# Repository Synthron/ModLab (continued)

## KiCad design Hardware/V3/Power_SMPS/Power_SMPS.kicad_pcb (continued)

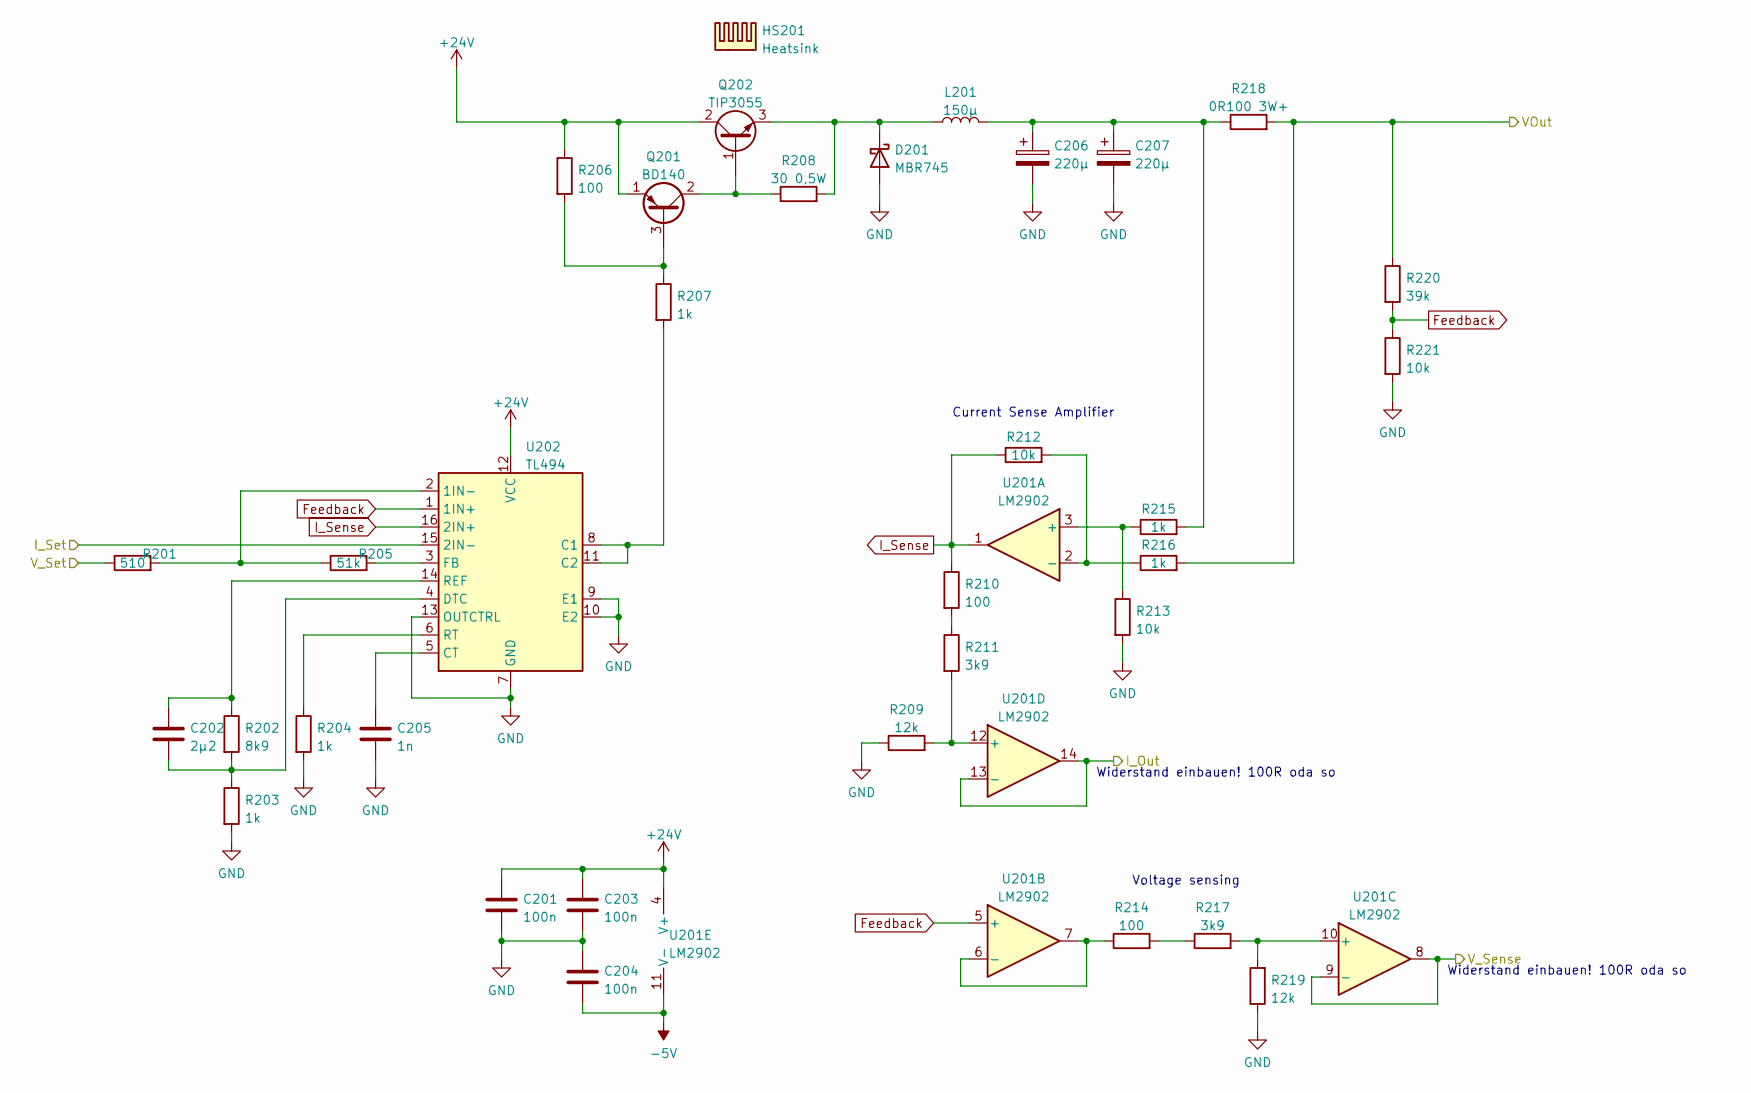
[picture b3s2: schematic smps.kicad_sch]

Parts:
C201, C203, C204: 100n; C_0805_2012Metric
C202: 2µ2; C_0805_2012Metric
C205: 1n; C_0805_2012Metric
C206, C207: 220µ; CP_Radial_D8.0mm_P5.00mm
D201: MBR745; TO-220-2_Vertical
HS201: Heatsink; SK574-50
L201: 150µ; L_Toroid_Vertical_L17.8mm_W8.1mm_P7.62mm_Bourns_5700
Q201: BD140; TO-126-3_Vertical
Q202: TIP3055; TO-218-3_Vertical
R201: 510; R_0805_2012Metric
R202: 8k9; R_0805_2012Metric
R203, R204, R207, R215, R216: 1k; R_0805_2012Metric
R205: 51k; R_0805_2012Metric
R206, R210, R214: 100; R_0805_2012Metric
R208: 30 0,5W; R_Axial_DIN0207_L6.3mm_D2.5mm_P10.16mm_Horizontal
R209, R219: 12k; R_0805_2012Metric
R211, R217: 3k9; R_0805_2012Metric
R212, R213, R221: 10k; R_0805_2012Metric
R218: 0R100 3W+; R_Axial_Power_L20.0mm_W6.4mm_P5.08mm_Vertical
R220: 39k; R_0805_2012Metric
U201: LM2902; TSSOP-14_4.4x5mm_P0.65mm
U202: TL494; SOIC-16_4.55x10.3mm_P1.27mm

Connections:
+24V: C201.1, C203.1, Q201.1 (E), Q202.2 (C), R206.1, U201.4 (V+), U202.12 (VCC); also elsewhere on the board
-5V: C204.2, U201.11 (V-); also elsewhere on the board
/CPU/I+: U201.13 (-), U201.14; also elsewhere on the board
/CPU/ISET: U202.15 (2IN-); also elsewhere on the board
/CPU/V+: U201.8, U201.9 (-); also elsewhere on the board
/CPU/VSET: R201.1; also elsewhere on the board
/SMPS/VOut: R216.2, R218.2, R220.1; also elsewhere on the board
Feedback: R220.2, R221.1, U201.5 (+), U202.1 (1IN+)
GND: C201.2, C203.2, C204.1, C205.2, C206.2, C207.2, D201.2 (A), R203.2, R204.2, R209.1, R213.2, R219.1, R221.2, U202.7 (GND), U202.9 (E1), U202.10 (E2), U202.13 (OUTCTRL); also elsewhere on the board
I_Sense: R210.1, R212.1, U201.1, U202.16 (2IN+)
unnamed: C202.1, R202.1, U202.14 (REF)
unnamed: C202.2, R202.2, R203.1, U202.4 (DTC)
unnamed: C205.1, U202.5 (CT)
unnamed: C206.1, C207.1, L201.2, R215.2, R218.1
unnamed: D201.1 (K), L201.1, Q202.3 (E), R208.2
unnamed: Q201.2 (C), Q202.1 (B), R208.1
unnamed: Q201.3 (B), R206.2, R207.1
unnamed: R201.2, R205.1, U202.2 (1IN-)
unnamed: R204.1, U202.6 (RT)
unnamed: R205.2, U202.3 (FB)
unnamed: R207.2, U202.8 (C1), U202.11 (C2)
unnamed: R209.2, R211.2, U201.12 (+)
unnamed: R210.2, R211.1
unnamed: R212.2, R216.1, U201.2 (-)
unnamed: R213.1, R215.1, U201.3 (+)
unnamed: R214.1, U201.6 (-), U201.7
unnamed: R214.2, R217.1
unnamed: R217.2, R219.2, U201.10 (+)

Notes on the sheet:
Widerstand einbauen! 100R oda so
Current Sense Amplifier
Voltage sensing

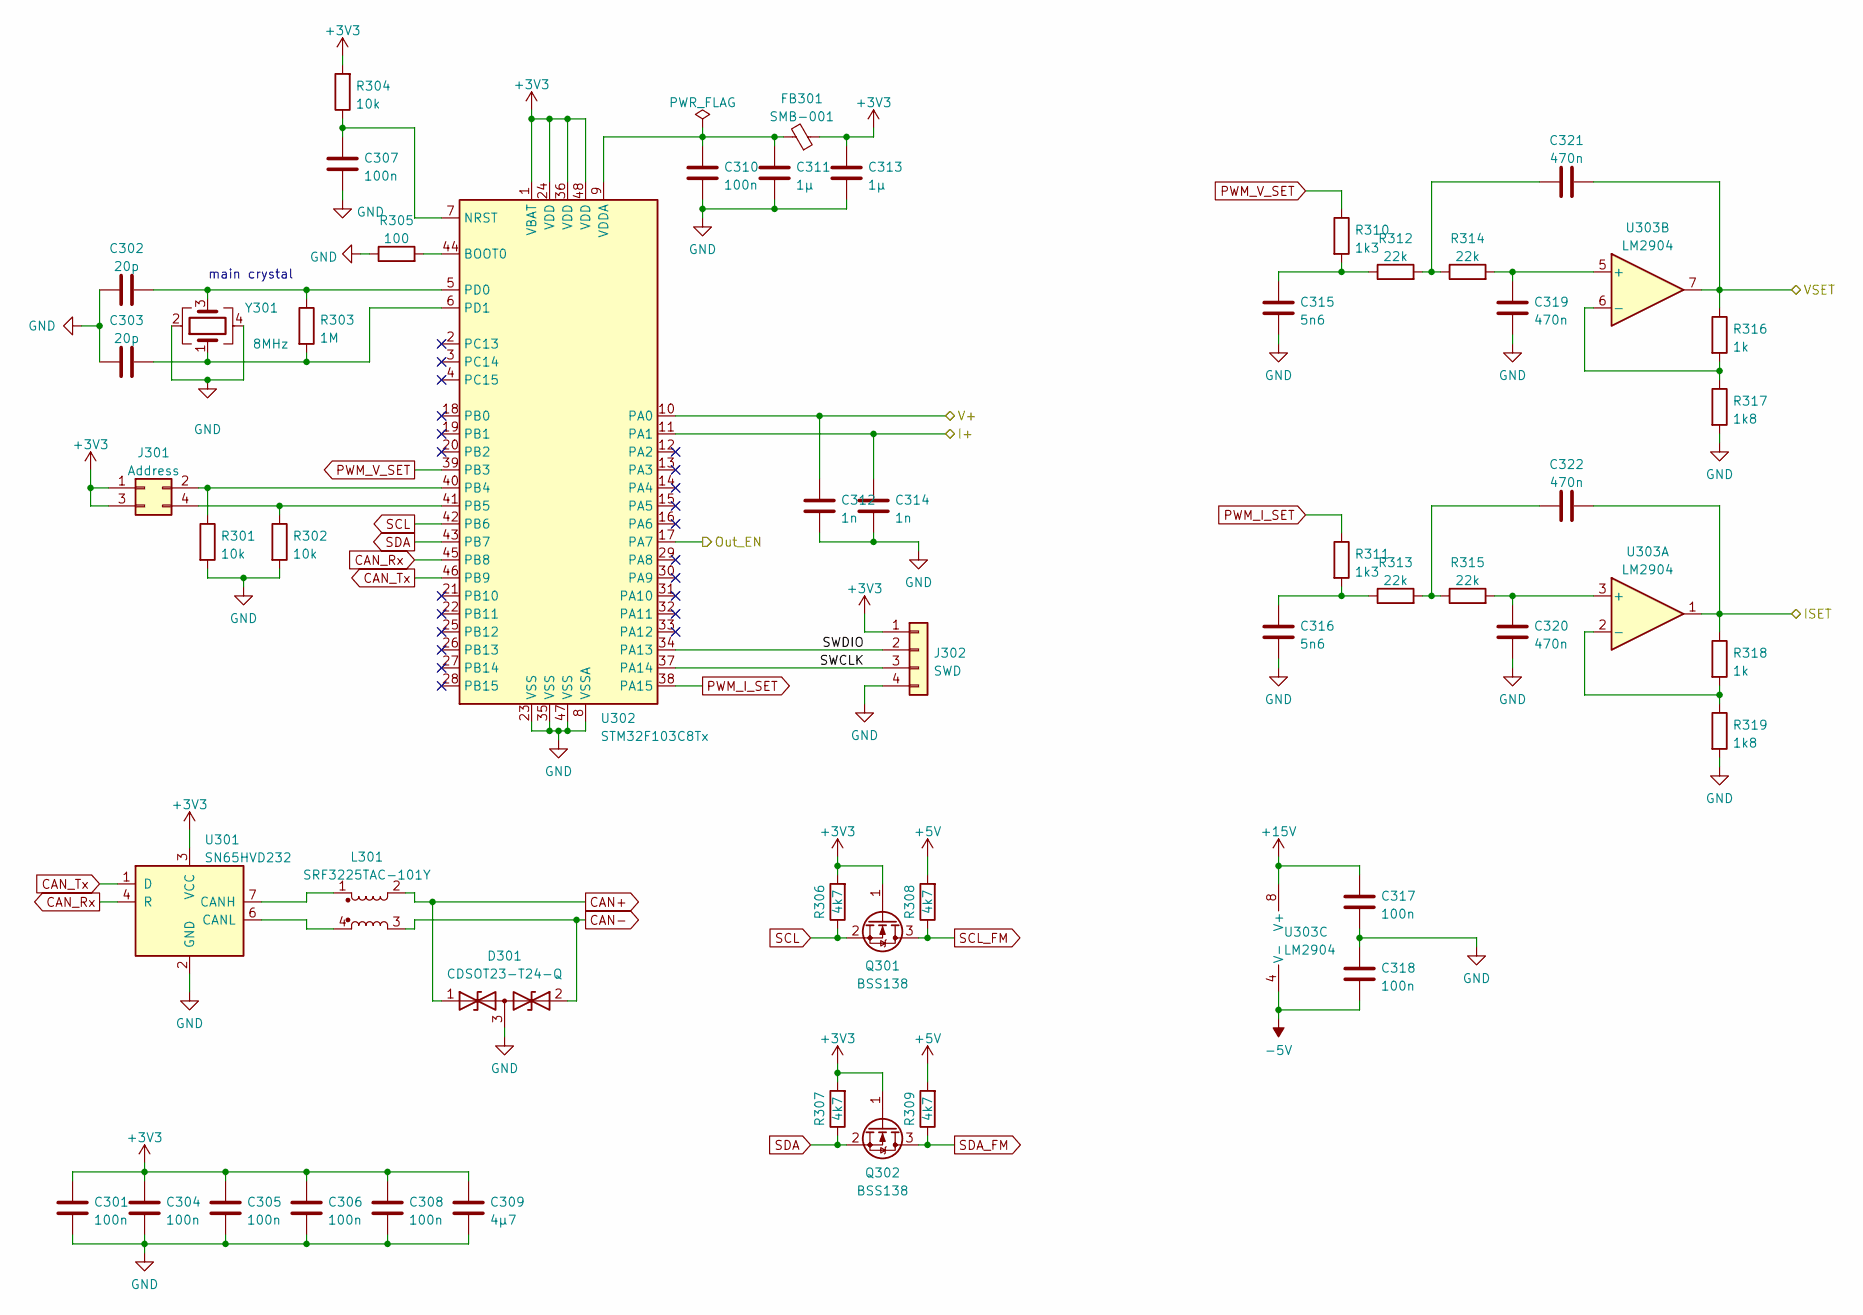
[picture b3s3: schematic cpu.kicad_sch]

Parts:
C301, C304, C305, C306, C307, C308, C310, C317, C318: 100n; C_0805_2012Metric
C302, C303: 20p; C_0805_2012Metric
C309: 4µ7; C_0805_2012Metric
C311, C313: 1µ; C_0805_2012Metric
C312, C314: 1n; C_0805_2012Metric
C315, C316: 5n6; C_0805_2012Metric
C319, C320, C321, C322: 470n; C_0805_2012Metric
D301: CDSOT23-T24-Q; SOT-23
FB301: SMB-001
J301: Address; PinHeader_2x02_P2.54mm_Vertical
J302: SWD; JST_XH_B4B-XH-A_1x04_P2.50mm_Vertical
L301: SRF3225TAC-101Y; SRF3225TAC
Q301, Q302: BSS138; SOT-23
R301, R302, R304: 10k; R_0805_2012Metric
R303: 1M; R_0805_2012Metric
R305: 100; R_0805_2012Metric
R306, R307, R308, R309: 4k7; R_0805_2012Metric
R310, R311: 1k3; R_0805_2012Metric
R312, R313, R314, R315: 22k; R_0805_2012Metric
R316, R318: 1k; R_0805_2012Metric
R317, R319: 1k8; R_0805_2012Metric
U301: SN65HVD232; SOIC-8_3.9x4.9mm_P1.27mm
U302: STM32F103C8Tx; LQFP-48_7x7mm_P0.5mm
U303: LM2904; SOIC-8_5.23x5.23mm_P1.27mm
Y301: 8MHz; Crystal_SMD_5032-4Pin_5.0x3.2mm

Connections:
+3V3: C301.1, C304.1, C305.1, C306.1, C308.1, C309.1, C313.1, FB301.1, J301.1, J301.3, J302.1, Q301.1 (G), Q302.1 (G), R304.2, R306.2, R307.2, U301.3 (VCC), U302.1 (VBAT), U302.24 (VDD), U302.36 (VDD), U302.48 (VDD); also elsewhere on the board
+5V: R308.2, R309.2; also elsewhere on the board
+15V: C317.1, U303.8 (V+); also elsewhere on the board
-5V: C318.2, U303.4 (V-); also elsewhere on the board
/CPU/I+: C314.1, U302.11 (PA1); also elsewhere on the board
/CPU/ISET: C322.2, R318.1, U303.1; also elsewhere on the board
/CPU/Out_EN: U302.17 (PA7); also elsewhere on the board
/CPU/SWCLK: J302.3, U302.37 (PA14)
/CPU/SWDIO: J302.2, U302.34 (PA13)
/CPU/V+: C312.1, U302.10 (PA0); also elsewhere on the board
/CPU/VSET: C321.2, R316.1, U303.7; also elsewhere on the board
CAN+: D301.1 (A1), L301.2; also elsewhere on the board
CAN-: D301.2 (A2), L301.3; also elsewhere on the board
CAN_Rx: U301.4 (R), U302.45 (PB8)
CAN_Tx: U301.1 (D), U302.46 (PB9)
GND: C301.2, C302.1, C303.1, C304.2, C305.2, C306.2, C307.2, C308.2, C309.2, C310.2, C311.2, C312.2, C313.2, C314.2, C315.2, C316.2, C317.2, C318.1, C319.2, C320.2, D301.3 (common), J302.4, R301.2, R302.2, R305.1, R317.2, R319.2, U301.2 (GND), U302.8 (VSSA), U302.23 (VSS), U302.35 (VSS), U302.47 (VSS), Y301.2, Y301.4; also elsewhere on the board
unnamed: C302.2, R303.1, U302.5 (PD0), Y301.3
unnamed: C303.2, R303.2, U302.6 (PD1), Y301.1
unnamed: C307.1, R304.1, U302.7 (NRST)
unnamed: C310.1, C311.1, FB301.2, U302.9 (VDDA)
unnamed: C315.1, R310.2, R312.1
unnamed: C316.1, R311.2, R313.1
unnamed: C319.1, R314.2, U303.5 (+)
unnamed: C320.1, R315.2, U303.3 (+)
unnamed: C321.1, R312.2, R314.1
unnamed: C322.1, R313.2, R315.1
unnamed: J301.2, R301.1, U302.40 (PB4)
unnamed: J301.4, R302.1, U302.41 (PB5)
unnamed: L301.1, U301.7 (CANH)
unnamed: L301.4, U301.6 (CANL)
unnamed: R305.2, U302.44 (BOOT0)
unnamed: R316.2, R317.1, U303.6 (-)
unnamed: R318.2, R319.1, U303.2 (-)
PWM_I_SET: R311.1, U302.38 (PA15)
PWM_V_SET: R310.1, U302.39 (PB3)
SCL: Q301.2 (S), R306.1, U302.42 (PB6)
SCL_FM: Q301.3 (D), R308.1; also elsewhere on the board
SDA: Q302.2 (S), R307.1, U302.43 (PB7)
SDA_FM: Q302.3 (D), R309.1; also elsewhere on the board

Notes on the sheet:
main crystal

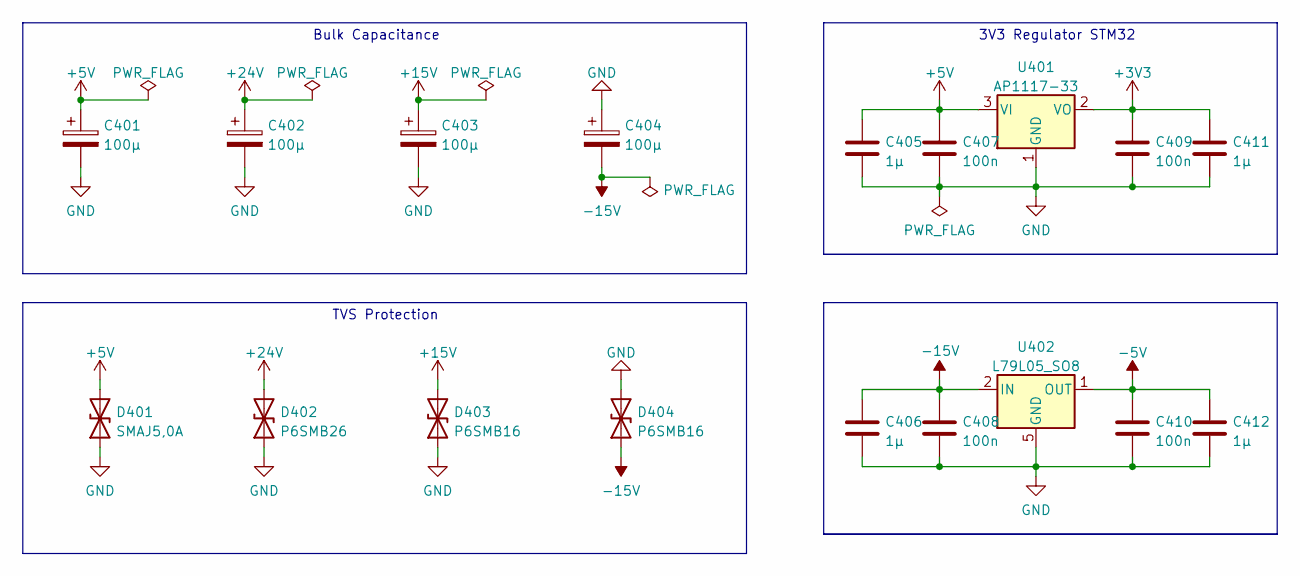
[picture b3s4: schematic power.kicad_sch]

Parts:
C401, C402, C403, C404: 100µ; CP_Radial_D8.0mm_P5.00mm
C405, C406, C411, C412: 1µ; C_0805_2012Metric
C407, C408, C409, C410: 100n; C_0805_2012Metric
D401: SMAJ5,0A; D_SMA
D402: P6SMB26; D_SMA
D403, D404: P6SMB16; D_SMA
U401: AP1117-33; SOT-223-3_TabPin2
U402: L79L05_SO8; SOIC-8_3.9x4.9mm_P1.27mm

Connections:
+3V3: C409.1, C411.1, U401.2 (VO); also elsewhere on the board
+5V: C401.1, C405.1, C407.1, D401.2 (A2), U401.3 (VI); also elsewhere on the board
+15V: C403.1, D403.2 (A2); also elsewhere on the board
+24V: C402.1, D402.2 (A2); also elsewhere on the board
-5V: C410.1, C412.1, U402.1 (OUT); also elsewhere on the board
-15V: C404.2, C406.1, C408.1, D404.1 (A1), U402.2 (IN), U402.3 (IN), U402.6 (IN), U402.7 (IN); also elsewhere on the board
GND: C401.2, C402.2, C403.2, C404.1, C405.2, C406.2, C407.2, C408.2, C409.2, C410.2, C411.2, C412.2, D401.1 (A1), D402.1 (A1), D403.1 (A1), D404.2 (A2), U401.1 (GND), U402.5 (GND); also elsewhere on the board

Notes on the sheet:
3V3 Regulator STM32
Bulk Capacitance
TVS Protection

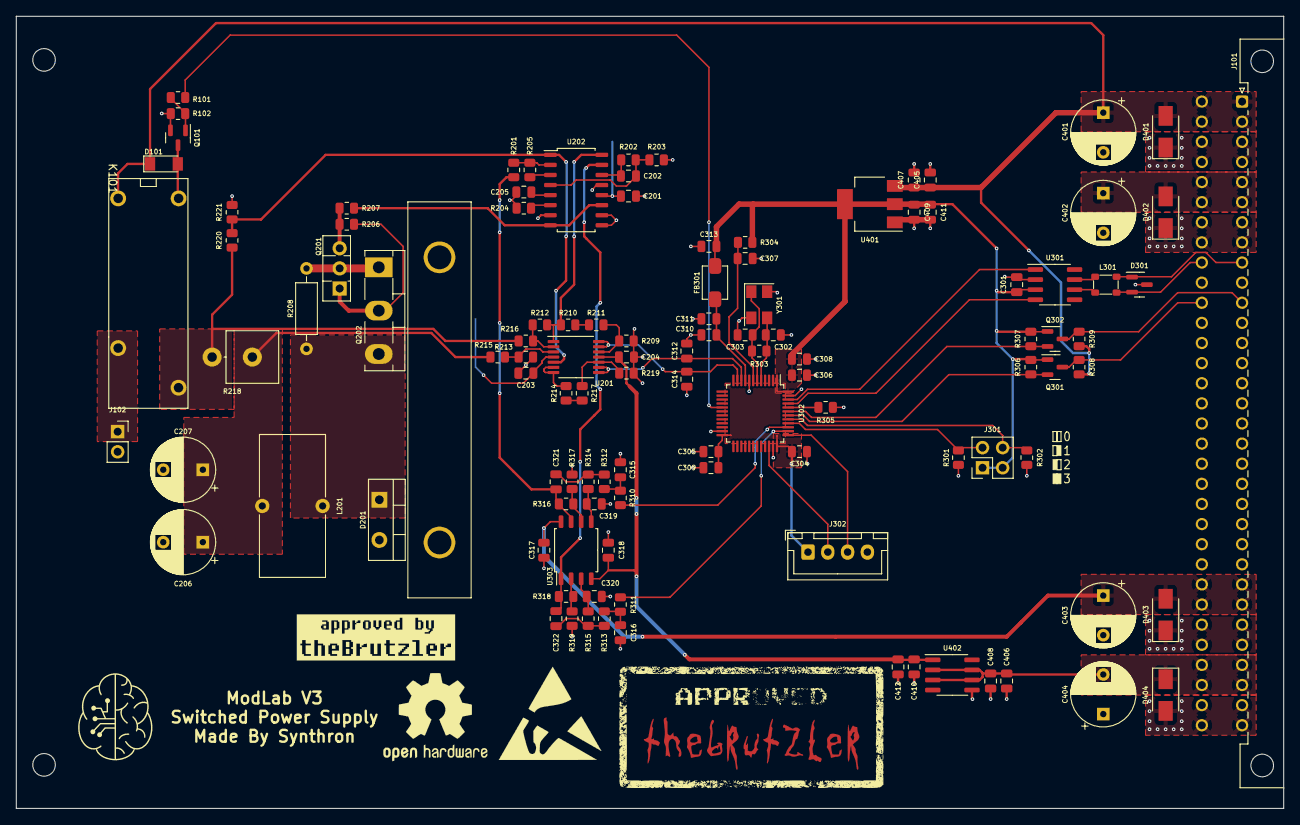
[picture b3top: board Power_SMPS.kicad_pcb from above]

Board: 2 copper layers, 160.0 x 100.0 mm, 112 parts (0 on the bottom side), 65 nets.

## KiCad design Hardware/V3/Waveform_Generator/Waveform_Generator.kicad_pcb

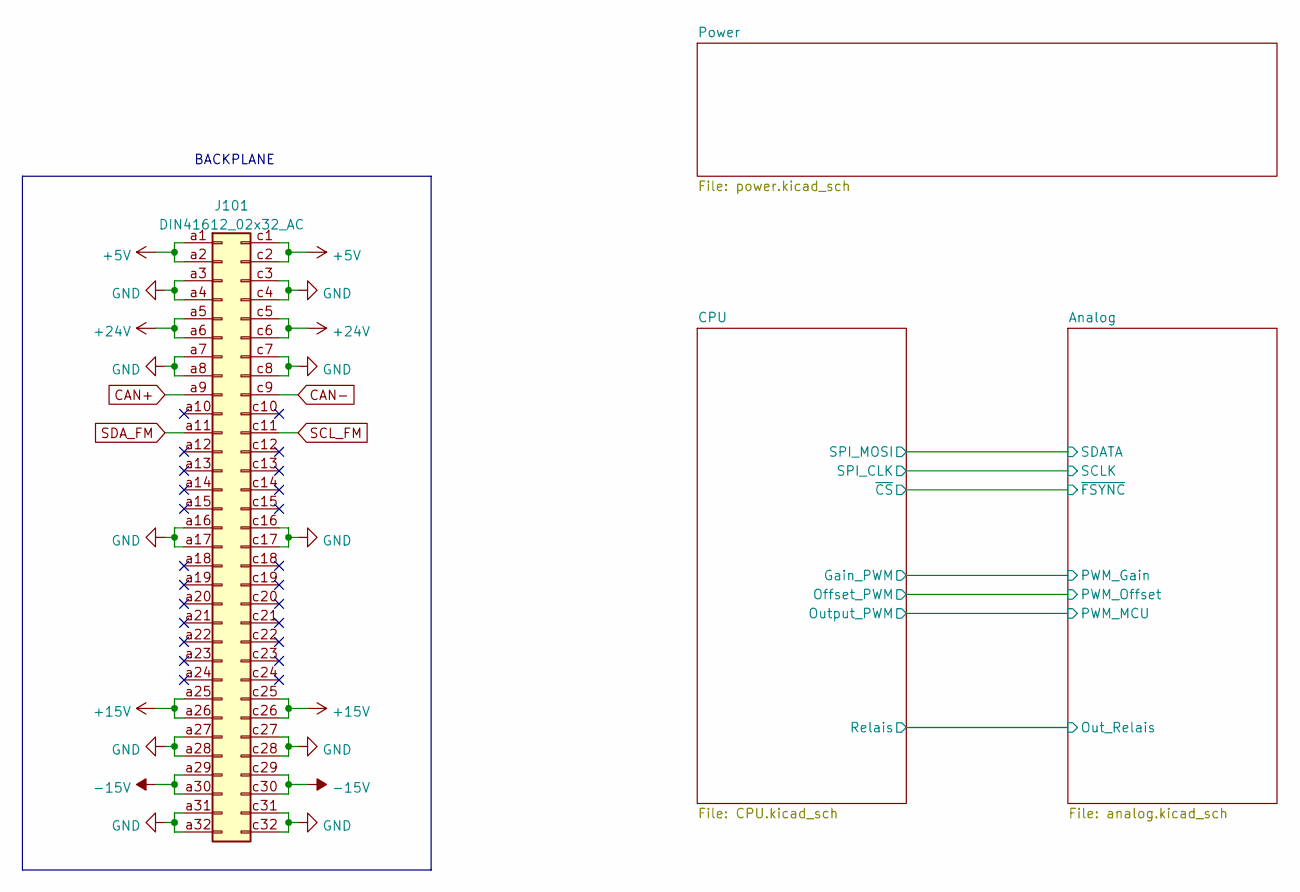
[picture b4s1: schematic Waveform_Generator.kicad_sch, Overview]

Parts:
J101: DIN41612_02x32_AC; VG64_Euro

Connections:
+5V: J101.a1, J101.a2, J101.c1, J101.c2; also elsewhere on the board
+15V: J101.a25, J101.a26, J101.c25, J101.c26; also elsewhere on the board
+24V: J101.a5, J101.a6, J101.c5, J101.c6; also elsewhere on the board
-15V: J101.a29, J101.a30, J101.c29, J101.c30; also elsewhere on the board
CAN+: J101.a9; also elsewhere on the board
CAN-: J101.c9; also elsewhere on the board
GND: J101.a3, J101.a4, J101.a7, J101.a8, J101.a16, J101.a17, J101.a27, J101.a28, J101.a31, J101.a32, J101.c3, J101.c4, J101.c7, J101.c8, J101.c16, J101.c17, J101.c27, J101.c28, J101.c31, J101.c32; also elsewhere on the board
SCL_FM: J101.c11; also elsewhere on the board
SDA_FM: J101.a11; also elsewhere on the board

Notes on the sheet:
BACKPLANE

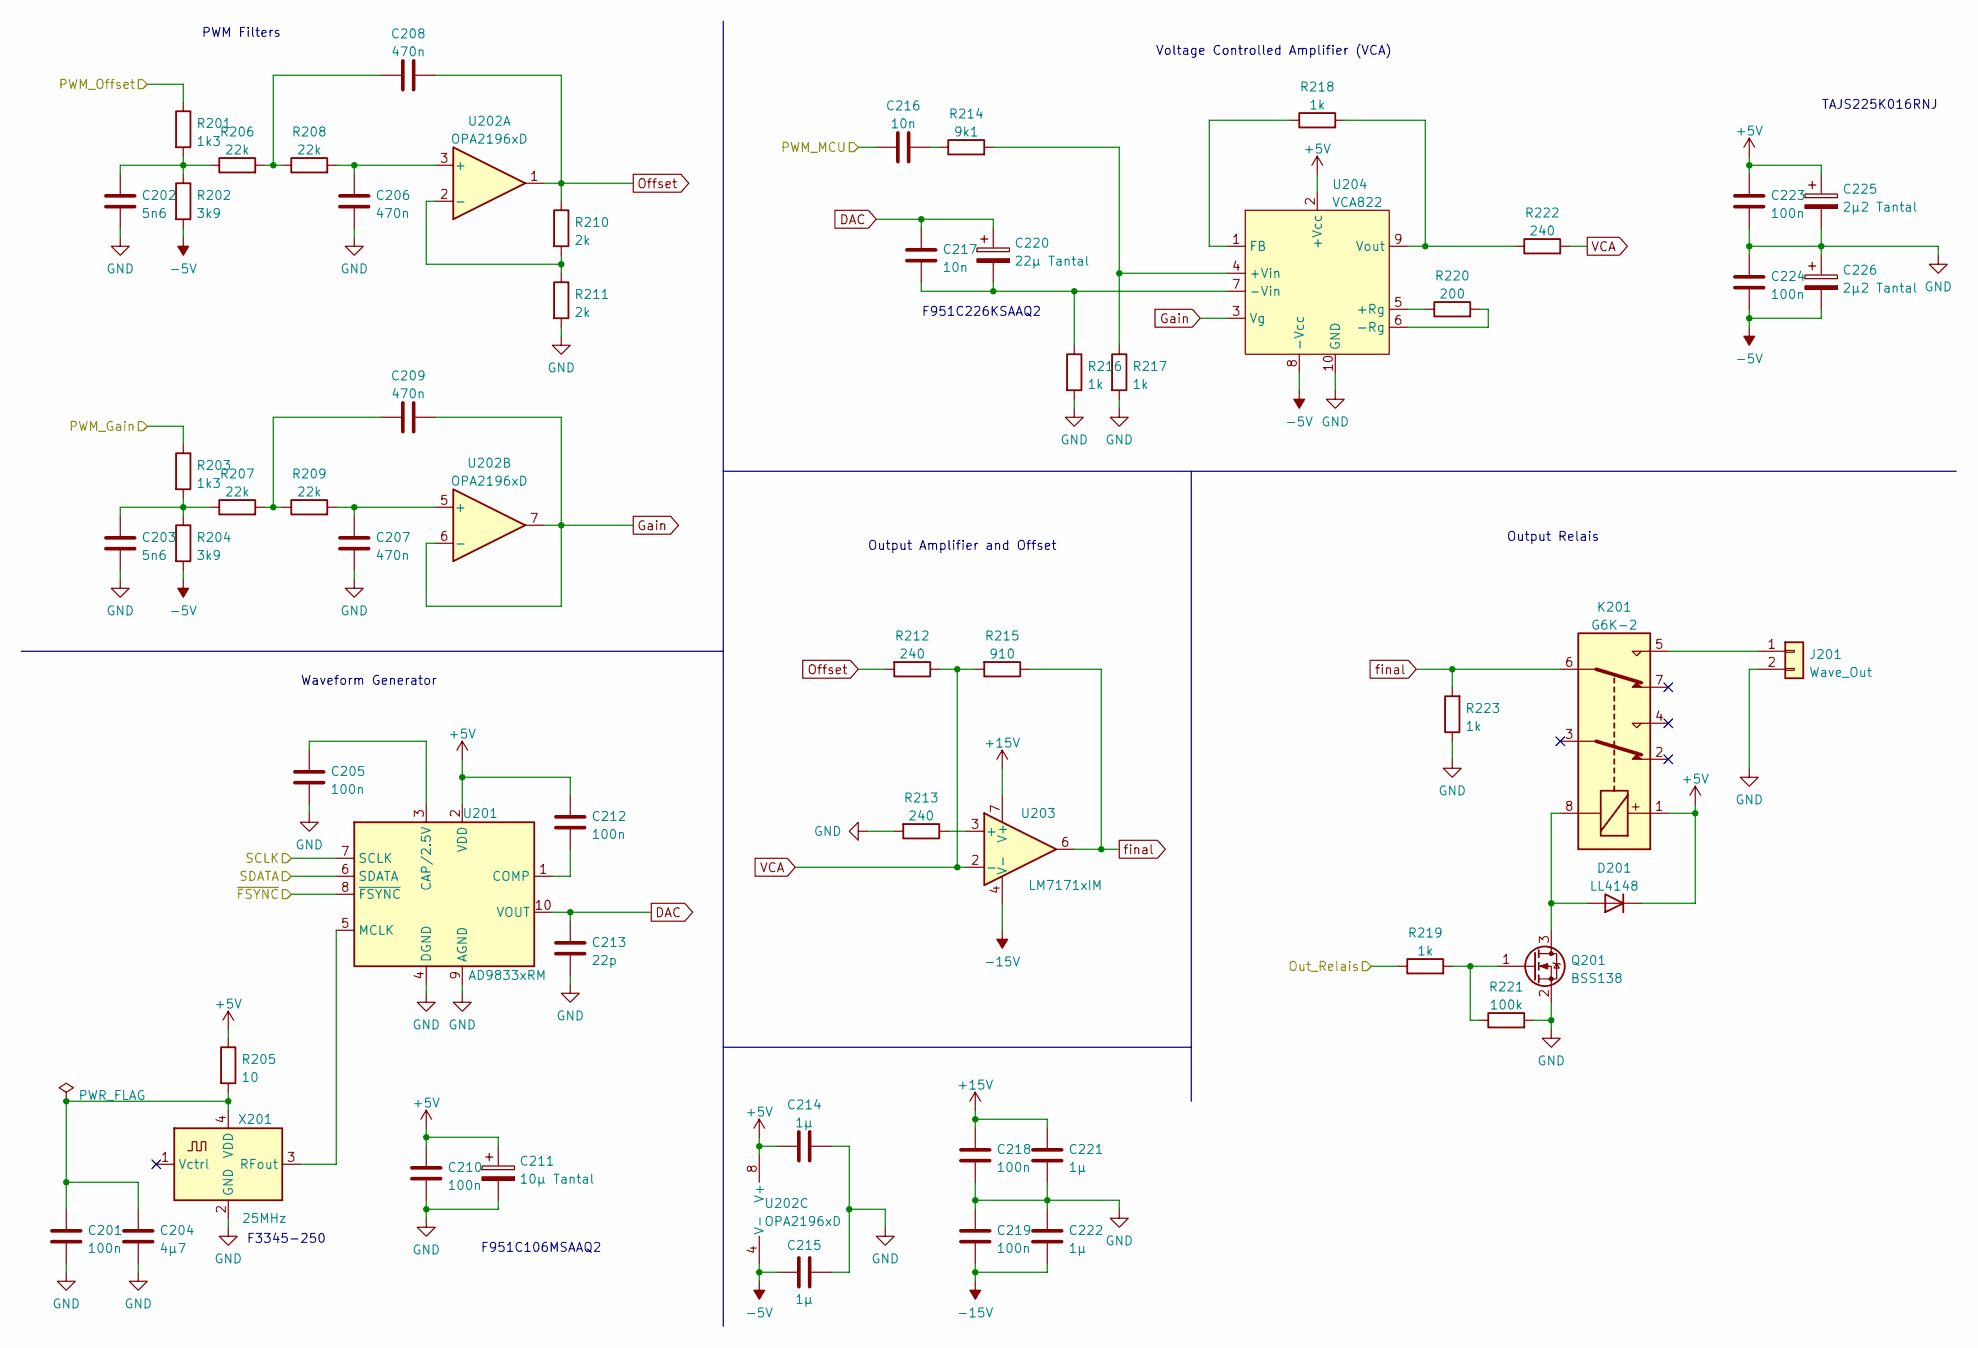
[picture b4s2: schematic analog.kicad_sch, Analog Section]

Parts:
C201, C205, C210, C212, C218, C219, C223, C224: 100n; C_0805_2012Metric
C202, C203: 5n6; C_0805_2012Metric
C204: 4µ7; C_0805_2012Metric
C206, C207, C208, C209: 470n; C_0805_2012Metric
C211: 10µ Tantal; CP_EIA-3216-12_Kemet-S
C213: 22p; C_0805_2012Metric
C214, C215, C221, C222: 1µ; C_0805_2012Metric
C216, C217: 10n; C_0805_2012Metric
C220: 22µ Tantal; CP_EIA-3216-12_Kemet-S
C225, C226: 2µ2 Tantal; CP_EIA-3216-12_Kemet-S
D201: LL4148; D_MiniMELF
J201: Wave_Out; PinSocket_1x02_P2.54mm_Vertical
K201: G6K-2; Relay_DPDT_Omron_G6K-2F
Q201: BSS138; SOT-23
R201, R203: 1k3; R_0805_2012Metric
R202, R204: 3k9; R_0805_2012Metric
R205: 10; R_0805_2012Metric
R206, R207, R208, R209: 22k; R_0805_2012Metric
R210, R211: 2k; R_0805_2012Metric
R212, R213, R222: 240; R_0805_2012Metric
R214: 9k1; R_0805_2012Metric
R215: 910; R_0805_2012Metric
R216, R217, R218, R219, R223: 1k; R_0805_2012Metric
R220: 200; R_0805_2012Metric
R221: 100k; R_0805_2012Metric
U201: AD9833xRM; MSOP-10_3x3mm_P0.5mm
U202: OPA2196xD; SOIC-8_3.9x4.9mm_P1.27mm
U203: LM7171xIM; SOIC-8_3.9x4.9mm_P1.27mm
U204: VCA822; MSOP-10_3x3mm_P0.5mm
X201: 25MHz; Oscillator_SMD_EuroQuartz_XO91-4Pin_7.0x5.0mm

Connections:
+5V: C210.1, C211.1, C212.1, C214.1, C223.1, C225.1, D201.1 (K), K201.1, R205.1, U201.2 (VDD), U202.8 (V+), U204.2 (+Vcc); also elsewhere on the board
+15V: C218.1, C221.1, U203.7 (V+); also elsewhere on the board
-5V: C215.1, C224.2, C226.2, R202.2, R204.2, U202.4 (V-), U204.8 (-Vcc); also elsewhere on the board
-15V: C219.2, C222.2, U203.4 (V-); also elsewhere on the board
/Analog/Out_Relais: R219.1; also elsewhere on the board
/Analog/PWM_Gain: R203.1; also elsewhere on the board
/Analog/PWM_MCU: C216.1; also elsewhere on the board
/Analog/PWM_Offset: R201.1; also elsewhere on the board
/Analog/SCLK: U201.7 (SCLK); also elsewhere on the board
/Analog/SDATA: U201.6 (SDATA); also elsewhere on the board
/Analog/~FSYNC: U201.8 (~FSYNC); also elsewhere on the board
DAC: C213.1, C217.1, C220.1, U201.10 (VOUT)
GND: C201.2, C202.2, C203.2, C204.2, C205.2, C206.2, C207.2, C210.2, C211.2, C213.2, C214.2, C215.2, C218.2, C219.1, C221.2, C222.1, C223.2, C224.1, C225.2, C226.1, J201.2, Q201.2 (S), R211.2, R213.2, R216.2, R217.2, R221.2, R223.1, U201.4 (DGND), U201.9 (AGND), U204.10 (GND), X201.2 (GND); also elsewhere on the board
Gain: C209.2, U202.6 (-), U202.7, U204.3 (Vg)
unnamed: C201.1, C204.1, R205.2, X201.4 (VDD)
unnamed: C202.1, R201.2, R202.1, R206.1
unnamed: C203.1, R203.2, R204.1, R207.1
unnamed: C205.1, U201.3 (CAP/2.5V)
unnamed: C206.1, R208.2, U202.3 (+)
unnamed: C207.1, R209.2, U202.5 (+)
unnamed: C208.1, R206.2, R208.1
unnamed: C209.1, R207.2, R209.1
unnamed: C212.2, U201.1 (COMP)
unnamed: C216.2, R214.1
unnamed: C217.2, C220.2, R216.1, U204.7 (-Vin)
unnamed: D201.2 (A), K201.8, Q201.3 (D)
unnamed: J201.1, K201.5
unnamed: Q201.1 (G), R219.2, R221.1
unnamed: R210.2, R211.1, U202.2 (-)
unnamed: R213.1, U203.3 (+)
unnamed: R214.2, R217.1, U204.4 (+Vin)
unnamed: R218.1, U204.1 (FB)
unnamed: R218.2, R222.1, U204.9 (Vout)
unnamed: R220.1, U204.5 (+Rg)
unnamed: R220.2, U204.6 (-Rg)
unnamed: U201.5 (MCLK), X201.3 (RFout)
Offset: C208.2, R210.1, R212.2, U202.1
VCA: R212.1, R215.2, R222.2, U203.2 (-)
final: K201.6, R215.1, R223.2, U203.6

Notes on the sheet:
PWM Filters
TAJS225K016RNJ
Output Amplifier and Offset
Waveform Generator
Voltage Controlled Amplifier (VCA)
F951C226KSAAQ2
Output Relais
F3345-250
F951C106MSAAQ2

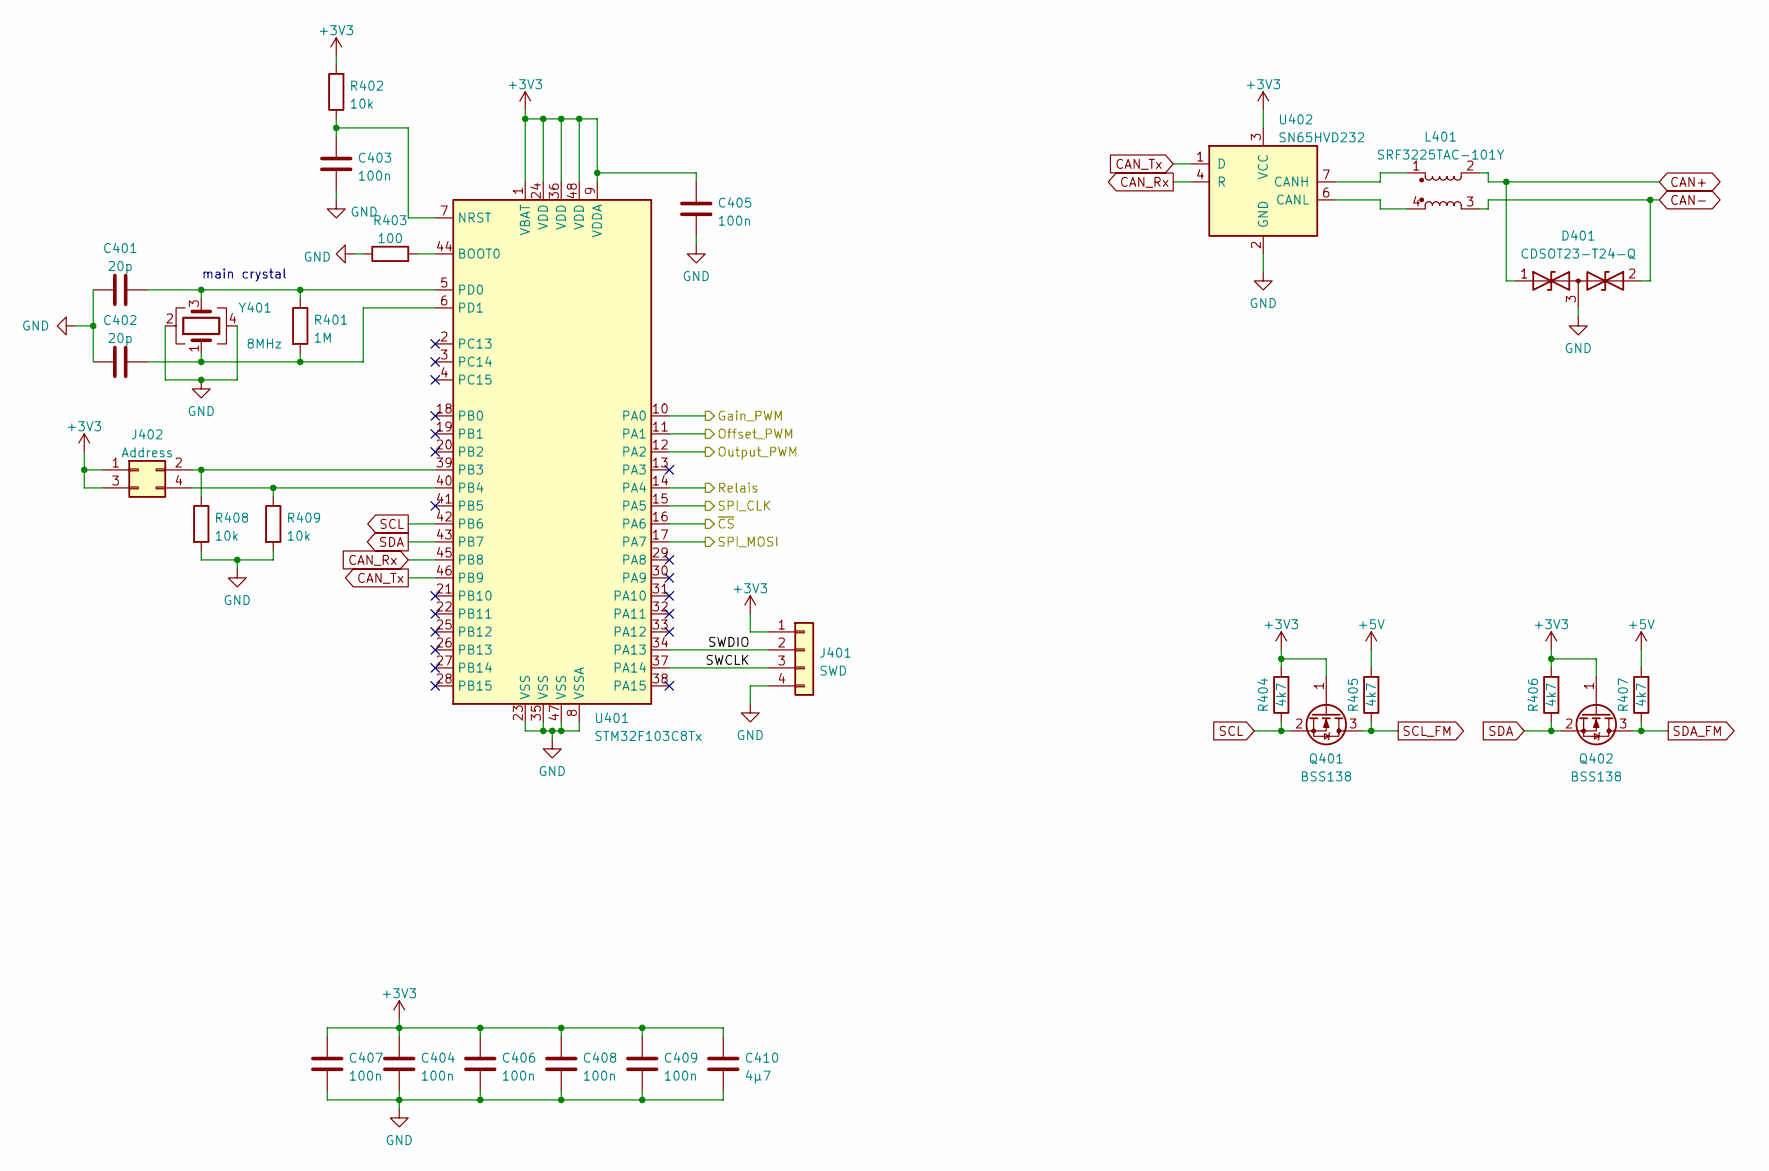
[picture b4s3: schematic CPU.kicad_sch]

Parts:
C401, C402: 20p; C_0805_2012Metric
C403, C404, C405, C406, C407, C408, C409: 100n; C_0805_2012Metric
C410: 4µ7; C_0805_2012Metric
D401: CDSOT23-T24-Q; SOT-23
J401: SWD; JST_XH_B4B-XH-A_1x04_P2.50mm_Vertical
J402: Address; PinHeader_2x02_P2.54mm_Vertical
L401: SRF3225TAC-101Y; SRF3225TAC
Q401, Q402: BSS138; SOT-23
R401: 1M; R_0805_2012Metric
R402, R408, R409: 10k; R_0805_2012Metric
R403: 100; R_0805_2012Metric
R404, R405, R406, R407: 4k7; R_0805_2012Metric
U401: STM32F103C8Tx; LQFP-48_7x7mm_P0.5mm
U402: SN65HVD232; SOIC-8_3.9x4.9mm_P1.27mm
Y401: 8MHz; Crystal_SMD_5032-4Pin_5.0x3.2mm

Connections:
+3V3: C404.1, C405.1, C406.1, C407.1, C408.1, C409.1, C410.1, J401.1, J402.1, J402.3, Q401.1 (G), Q402.1 (G), R402.2, R404.2, R406.2, U401.1 (VBAT), U401.9 (VDDA), U401.24 (VDD), U401.36 (VDD), U401.48 (VDD), U402.3 (VCC); also elsewhere on the board
+5V: R405.2, R407.2; also elsewhere on the board
/Analog/Out_Relais: U401.14 (PA4); also elsewhere on the board
/Analog/PWM_Gain: U401.10 (PA0); also elsewhere on the board
/Analog/PWM_MCU: U401.12 (PA2); also elsewhere on the board
/Analog/PWM_Offset: U401.11 (PA1); also elsewhere on the board
/Analog/SCLK: U401.15 (PA5); also elsewhere on the board
/Analog/SDATA: U401.17 (PA7); also elsewhere on the board
/Analog/~FSYNC: U401.16 (PA6); also elsewhere on the board
/CPU/SWCLK: J401.3, U401.37 (PA14)
/CPU/SWDIO: J401.2, U401.34 (PA13)
CAN+: D401.1 (A1), L401.2; also elsewhere on the board
CAN-: D401.2 (A2), L401.3; also elsewhere on the board
CAN_Rx: U401.45 (PB8), U402.4 (R)
CAN_Tx: U401.46 (PB9), U402.1 (D)
GND: C401.1, C402.1, C403.2, C404.2, C405.2, C406.2, C407.2, C408.2, C409.2, C410.2, D401.3 (common), J401.4, R403.1, R408.2, R409.2, U401.8 (VSSA), U401.23 (VSS), U401.35 (VSS), U401.47 (VSS), U402.2 (GND), Y401.2, Y401.4; also elsewhere on the board
unnamed: C401.2, R401.1, U401.5 (PD0), Y401.3
unnamed: C402.2, R401.2, U401.6 (PD1), Y401.1
unnamed: C403.1, R402.1, U401.7 (NRST)
unnamed: J402.2, R408.1, U401.39 (PB3)
unnamed: J402.4, R409.1, U401.40 (PB4)
unnamed: L401.1, U402.7 (CANH)
unnamed: L401.4, U402.6 (CANL)
unnamed: R403.2, U401.44 (BOOT0)
SCL: Q401.2 (S), R404.1, U401.42 (PB6)
SCL_FM: Q401.3 (D), R405.1; also elsewhere on the board
SDA: Q402.2 (S), R406.1, U401.43 (PB7)
SDA_FM: Q402.3 (D), R407.1; also elsewhere on the board

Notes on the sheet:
main crystal

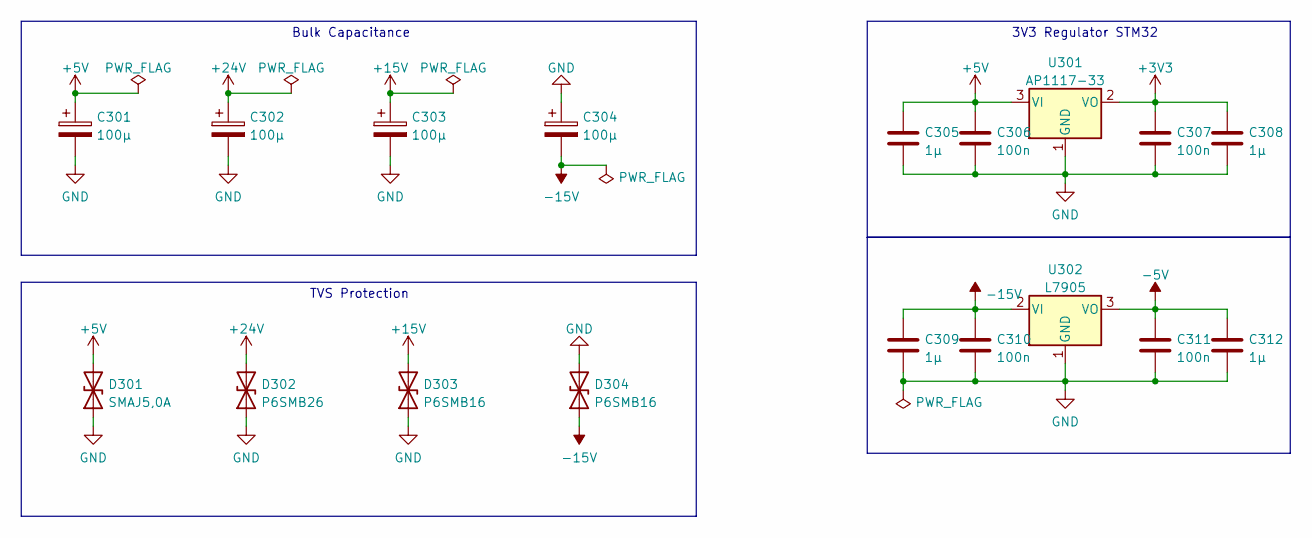
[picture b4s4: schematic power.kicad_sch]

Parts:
C301, C302, C303, C304: 100µ; CP_Radial_D8.0mm_P5.00mm
C305, C308, C309, C312: 1µ; C_0805_2012Metric
C306, C307, C310, C311: 100n; C_0805_2012Metric
D301: SMAJ5,0A; D_SMA
D302: P6SMB26; D_SMA
D303, D304: P6SMB16; D_SMA
U301: AP1117-33; SOT-223-3_TabPin2
U302: L7905; TO-263-2

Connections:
+3V3: C307.1, C308.1, U301.2 (VO); also elsewhere on the board
+5V: C301.1, C305.1, C306.1, D301.2 (A2), U301.3 (VI); also elsewhere on the board
+15V: C303.1, D303.2 (A2); also elsewhere on the board
+24V: C302.1, D302.2 (A2); also elsewhere on the board
-5V: C311.1, C312.1, U302.3 (VO); also elsewhere on the board
-15V: C304.2, C309.1, C310.1, D304.1 (A1), U302.2 (VI); also elsewhere on the board
GND: C301.2, C302.2, C303.2, C304.1, C305.2, C306.2, C307.2, C308.2, C309.2, C310.2, C311.2, C312.2, D301.1 (A1), D302.1 (A1), D303.1 (A1), D304.2 (A2), U301.1 (GND), U302.1 (GND); also elsewhere on the board

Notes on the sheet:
3V3 Regulator STM32
Bulk Capacitance
TVS Protection

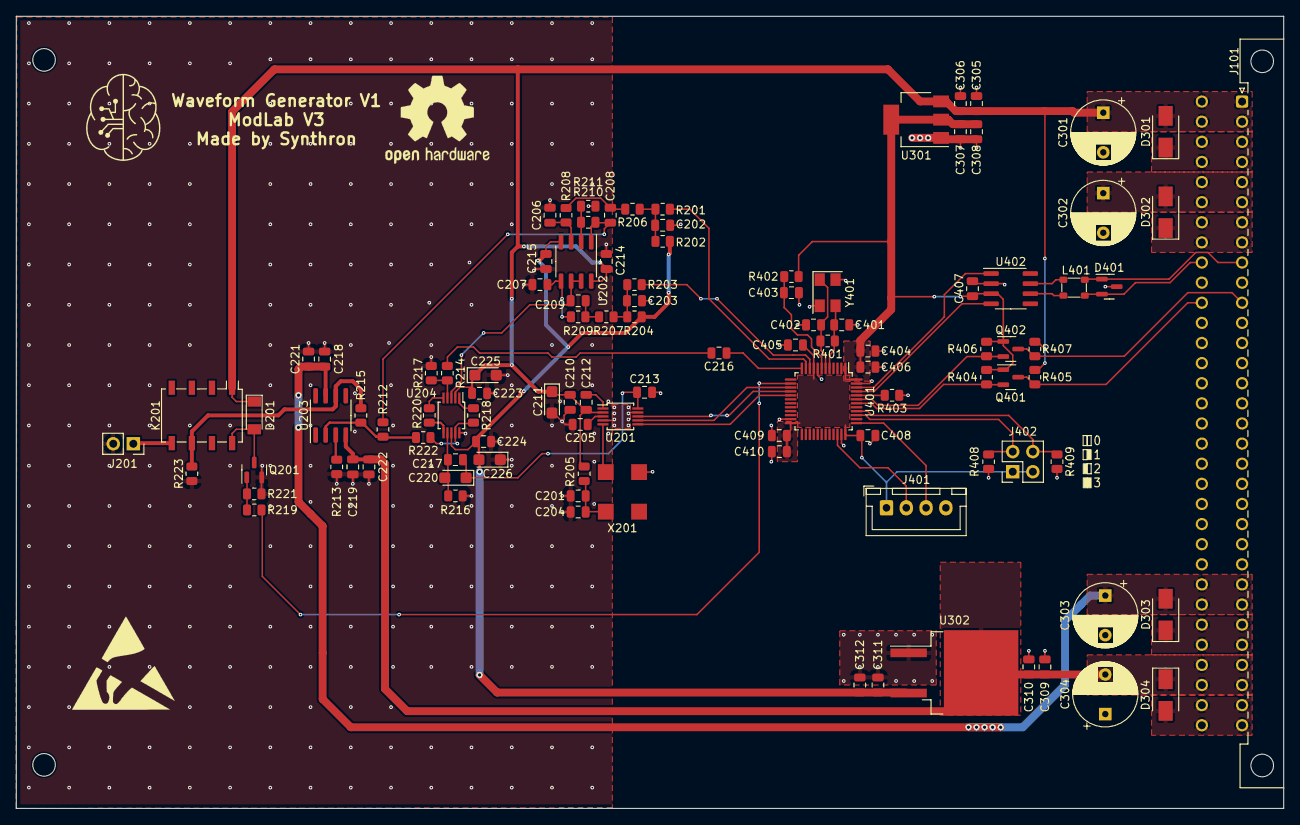
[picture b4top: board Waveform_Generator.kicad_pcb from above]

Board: 2 copper layers, 160.0 x 100.0 mm, 105 parts (0 on the bottom side), 59 nets.
